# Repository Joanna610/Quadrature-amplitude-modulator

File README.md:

# Quadrature-amplitude-modulator

The goal of the project was to create two devices that would be wirelessly communicating with each other in simplex mode, using quadrature amplitude modulation at the 433 MHz band.

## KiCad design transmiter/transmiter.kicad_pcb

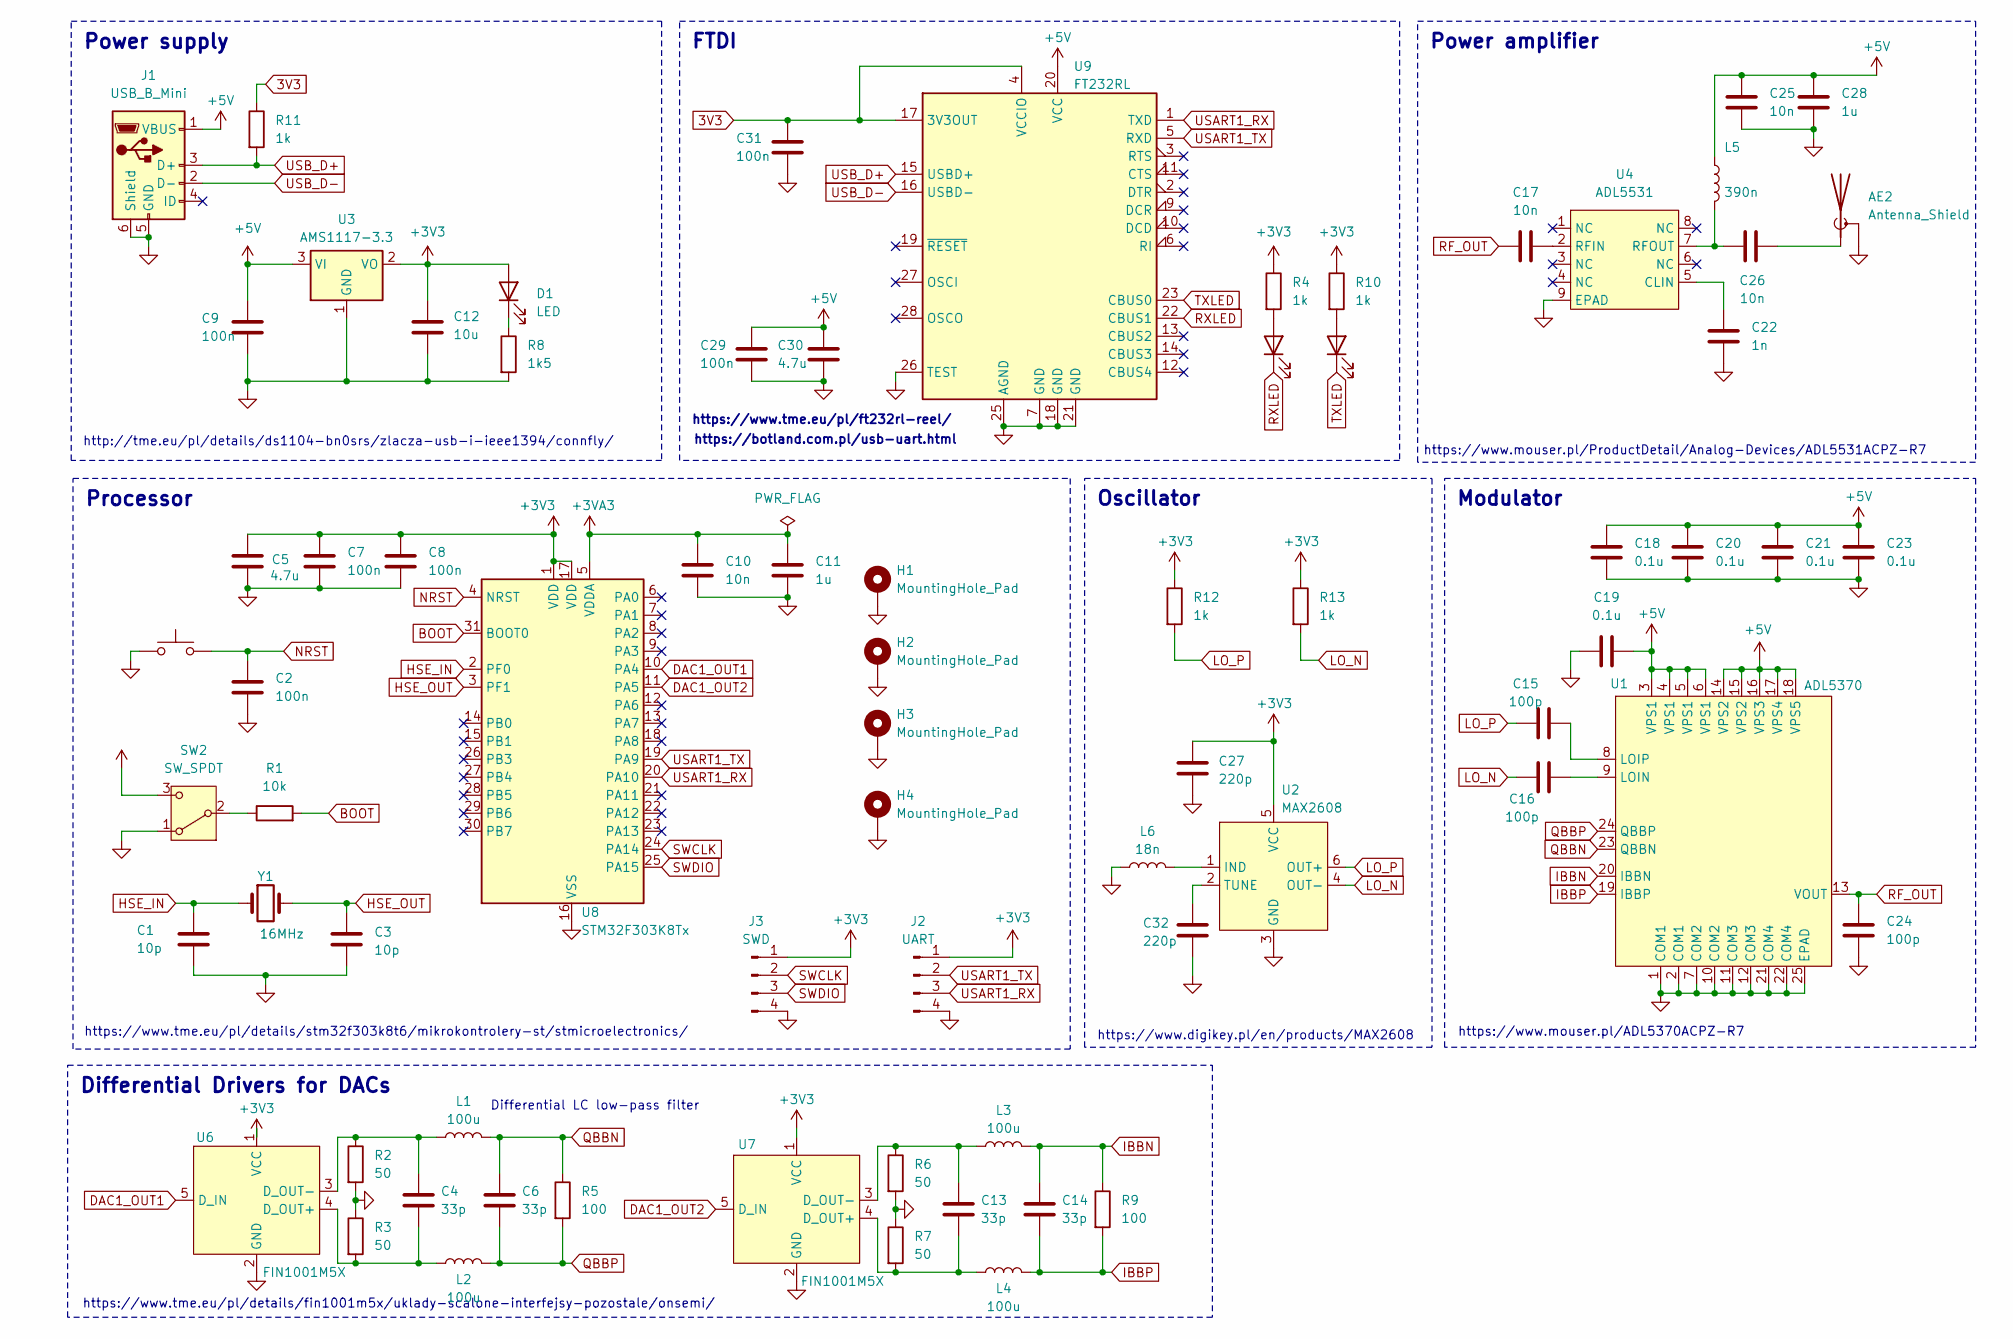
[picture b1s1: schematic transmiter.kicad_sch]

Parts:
AE2: Antenna_Shield; U.FL_Molex_MCRF_73412-0110_Vertical
C1, C3: 10p; C_0603_1608Metric_Pad1.08x0.95mm_HandSolder
C2, C7, C8, C9, C29, C31: 100n; C_0603_1608Metric_Pad1.08x0.95mm_HandSolder
C4, C6, C13, C14: 33p; C_0603_1608Metric_Pad1.08x0.95mm_HandSolder
C5, C30: 4.7u; C_0603_1608Metric_Pad1.08x0.95mm_HandSolder
C10, C25: 10n; C_0603_1608Metric_Pad1.08x0.95mm_HandSolder
C11, C28: 1u; C_0603_1608Metric_Pad1.08x0.95mm_HandSolder
C12: 10u; C_0603_1608Metric_Pad1.08x0.95mm_HandSolder
C15, C16, C24: 100p; C_0402_1005Metric_Pad0.74x0.62mm_HandSolder
C17, C26: 10n; C_0402_1005Metric_Pad0.74x0.62mm_HandSolder
C18, C19, C20, C21, C23: 0.1u; C_0402_1005Metric_Pad0.74x0.62mm_HandSolder
C22: 1n; C_0603_1608Metric_Pad1.08x0.95mm_HandSolder
C27, C32: 220p; C_0603_1608Metric_Pad1.08x0.95mm_HandSolder
D1, D2, D3: LED; LED_0805_2012Metric_Pad1.15x1.40mm_HandSolder
H1, H2, H3, H4: MountingHole_Pad; MountingHole_2.2mm_M2_DIN965_Pad
J1: USB_B_Mini; USB_Mini-B_Lumberg_2486_01_Horizontal
J2: UART; PinHeader_1x04_P2.54mm_Vertical
J3: SWD; PinHeader_1x04_P2.54mm_Vertical
L1, L2, L3, L4: 100u; L_1210_3225Metric_Pad1.42x2.65mm_HandSolder
L5: 390n; L_1008_2520Metric_Pad1.43x2.20mm_HandSolder
L6: 18n; L_0603_1608Metric_Pad1.05x0.95mm_HandSolder
R1: 10k; R_0603_1608Metric_Pad0.98x0.95mm_HandSolder
R2, R3, R6, R7: 50; R_0603_1608Metric_Pad0.98x0.95mm_HandSolder
R4, R10, R11, R12, R13: 1k; R_0603_1608Metric_Pad0.98x0.95mm_HandSolder
R5, R9: 100; R_0603_1608Metric_Pad0.98x0.95mm_HandSolder
R8: 1k5; R_0603_1608Metric_Pad0.98x0.95mm_HandSolder
SW1: SW_Push; PUSH
SW2: SW_SPDT; Nidec_Copal_CAS-120A
U1: ADL5370; LFCSP-24-1EP_4x4mm_P0.5mm_EP2.3x2.3mm
U2: MAX2608; SOT-23-6
U3: AMS1117-3.3; SOT-223-3_TabPin2
U4: ADL5531; LFCSP-8-1EP_3x3mm_P0.5mm_EP1.45x1.74mm
U6, U7: FIN1001M5X; SOT-23-5_HandSoldering
U8: STM32F303K8Tx; LQFP-32_7x7mm_P0.8mm
U9: FT232RL; SSOP-28_5.3x10.2mm_P0.65mm
Y1: 16MHz; Crystal_HC49-4H_Vertical

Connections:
3V3: C31.2, R11.1, U9.4 (VCCIO), U9.17 (3V3OUT)
+3V3: C5.1, C7.1, C8.1, C12.1, C27.2, D1.2 (A), J2.1, J3.1, R4.1, R10.1, R12.1, R13.1, SW2.3 (C), U2.5 (VCC), U3.2 (VO), U6.1 (VCC), U7.1 (VCC), U8.1 (VDD), U8.17 (VDD)
+3VA3: C10.1, C11.1, U8.5 (VDDA)
+5V: C9.2, C18.2, C19.1, C20.2, C21.2, C23.2, C25.1, C28.1, C29.2, C30.2, J1.1 (VBUS), L5.1, U1.3 (VPS1), U1.4 (VPS1), U1.5 (VPS1), U1.6 (VPS1), U1.14 (VPS2), U1.15 (VPS2), U1.16 (VPS3), U1.17 (VPS4), U1.18 (VPS5), U3.3 (VI), U9.20 (VCC)
BOOT: R1.2, U8.31 (BOOT0)
DAC1_OUT1: U6.5 (D_IN), U8.10 (PA4)
DAC1_OUT2: U7.5 (D_IN), U8.11 (PA5)
GND: AE2.2 (Shield), C1.2, C2.2, C3.2, C5.2, C7.2, C8.2, C9.1, C10.2, C11.2, C12.2, C18.1, C19.2, C20.1, C21.1, C22.2, C23.1, C24.2, C25.2, C27.1, C28.2, C29.1, C30.1, C31.1, C32.1, H1.1, H2.1, H3.1, H4.1, J1.5 (GND), J1.6 (Shield), J2.4, J3.4, L6.1, R2.2, R3.1, R6.2, R7.1, R8.2, SW1.1, SW2.1 (A), U1.1 (COM1), U1.2 (COM1), U1.7 (COM2), U1.10 (COM2), U1.11 (COM3), U1.12 (COM3), U1.21 (COM4), U1.22 (COM4), U1.25 (EPAD), U2.3 (GND), U3.1 (GND), U4.9 (EPAD), U6.2 (GND), U7.2 (GND), U8.16 (VSS), U8.32 (VSS), U9.7 (GND), U9.18 (GND), U9.21 (GND), U9.25 (AGND), U9.26 (TEST)
HSE_IN: C1.1, U8.2 (PF0), Y1.1
HSE_OUT: C3.1, U8.3 (PF1), Y1.2
IBBN: C14.1, L3.2, R9.1, U1.20 (IBBN)
IBBP: C14.2, L4.2, R9.2, U1.19 (IBBP)
LO_N: C16.1, R13.2, U2.4 (OUT-)
LO_P: C15.1, R12.2, U2.6 (OUT+)
NRST: C2.1, SW1.2, U8.4 (NRST)
unnamed: AE2.1 (A), C26.2
unnamed: D1.1 (K), R8.1
unnamed: D2.2 (A), R4.2
unnamed: D3.2 (A), R10.2
unnamed: R1.1, SW2.2 (B)
unnamed: C16.2, U1.9 (LOIN)
unnamed: C15.2, U1.8 (LOIP)
unnamed: L6.2, U2.1 (IND)
unnamed: C32.2, U2.2 (TUNE)
unnamed: C22.1, U4.5 (CLIN)
unnamed: C17.2, U4.2 (RFIN)
unnamed: C26.1, L5.2, U4.7 (RFOUT)
unnamed: C4.2, L2.1, R3.2, U6.4 (D_OUT+)
unnamed: C4.1, L1.1, R2.1, U6.3 (D_OUT-)
unnamed: C13.2, L4.1, R7.2, U7.4 (D_OUT+)
unnamed: C13.1, L3.1, R6.1, U7.3 (D_OUT-)
QBBN: C6.1, L1.2, R5.1, U1.23 (QBBN)
QBBP: C6.2, L2.2, R5.2, U1.24 (QBBP)
RF_OUT: C17.1, C24.1, U1.13 (VOUT)
RXLED: D2.1 (K), U9.22 (CBUS1)
SWCLK: J3.2, U8.24 (PA14)
SWDIO: J3.3, U8.25 (PA15)
TXLED: D3.1 (K), U9.23 (CBUS0)
USART1_RX: J2.3, U8.20 (PA10), U9.1 (TXD)
USART1_TX: J2.2, U8.19 (PA9), U9.5 (RXD)
USB_D+: J1.3 (D+), R11.2, U9.15 (USBD+)
USB_D-: J1.2 (D-), U9.16 (USBD-)

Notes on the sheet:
Oscillator
Power amplifier
Processor
Differential Drivers for DACs
FTDI
Power supply
Modulator
https://www.digikey.pl/en/products/MAX2608
Differential LC low-pass filter
https://www.tme.eu/pl/ft232rl-reel/
https://www.mouser.pl/ProductDetail/Analog-Devices/ADL5531ACPZ-R7
https://www.tme.eu/pl/details/fin1001m5x/uklady-scalone-interfejsy-pozostale/onsemi/
https://www.mouser.pl/ADL5370ACPZ-R7
https://botland.com.pl/usb-uart.html
https://www.tme.eu/pl/details/stm32f303k8t6/mikrokontrolery-st/stmicroelectronics/
http://tme.eu/pl/details/ds1104-bn0srs/zlacza-usb-i-ieee1394/connfly/

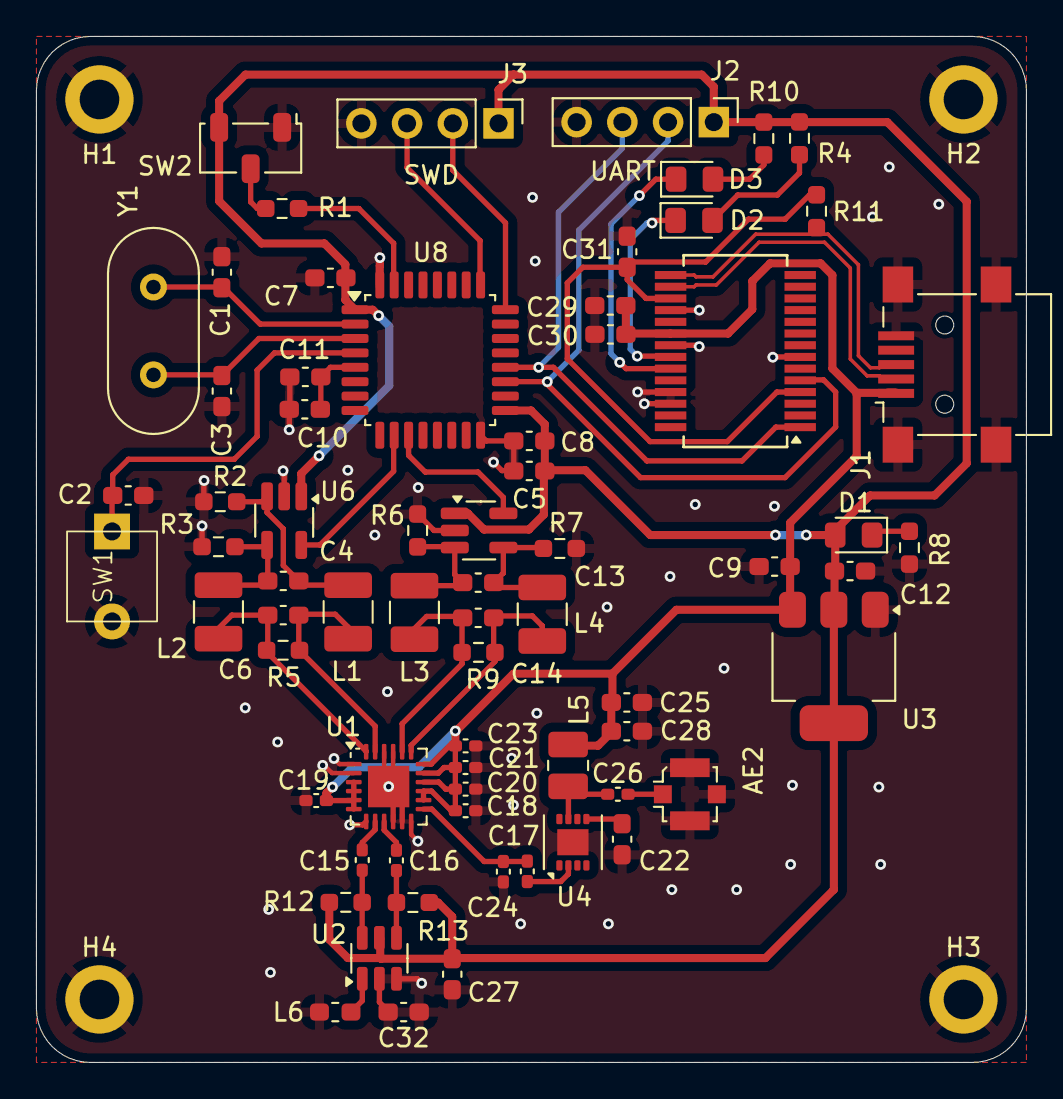
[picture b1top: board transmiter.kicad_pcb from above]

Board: 2 copper layers, 55.0 x 57.0 mm, 73 parts (0 on the bottom side), 42 nets.

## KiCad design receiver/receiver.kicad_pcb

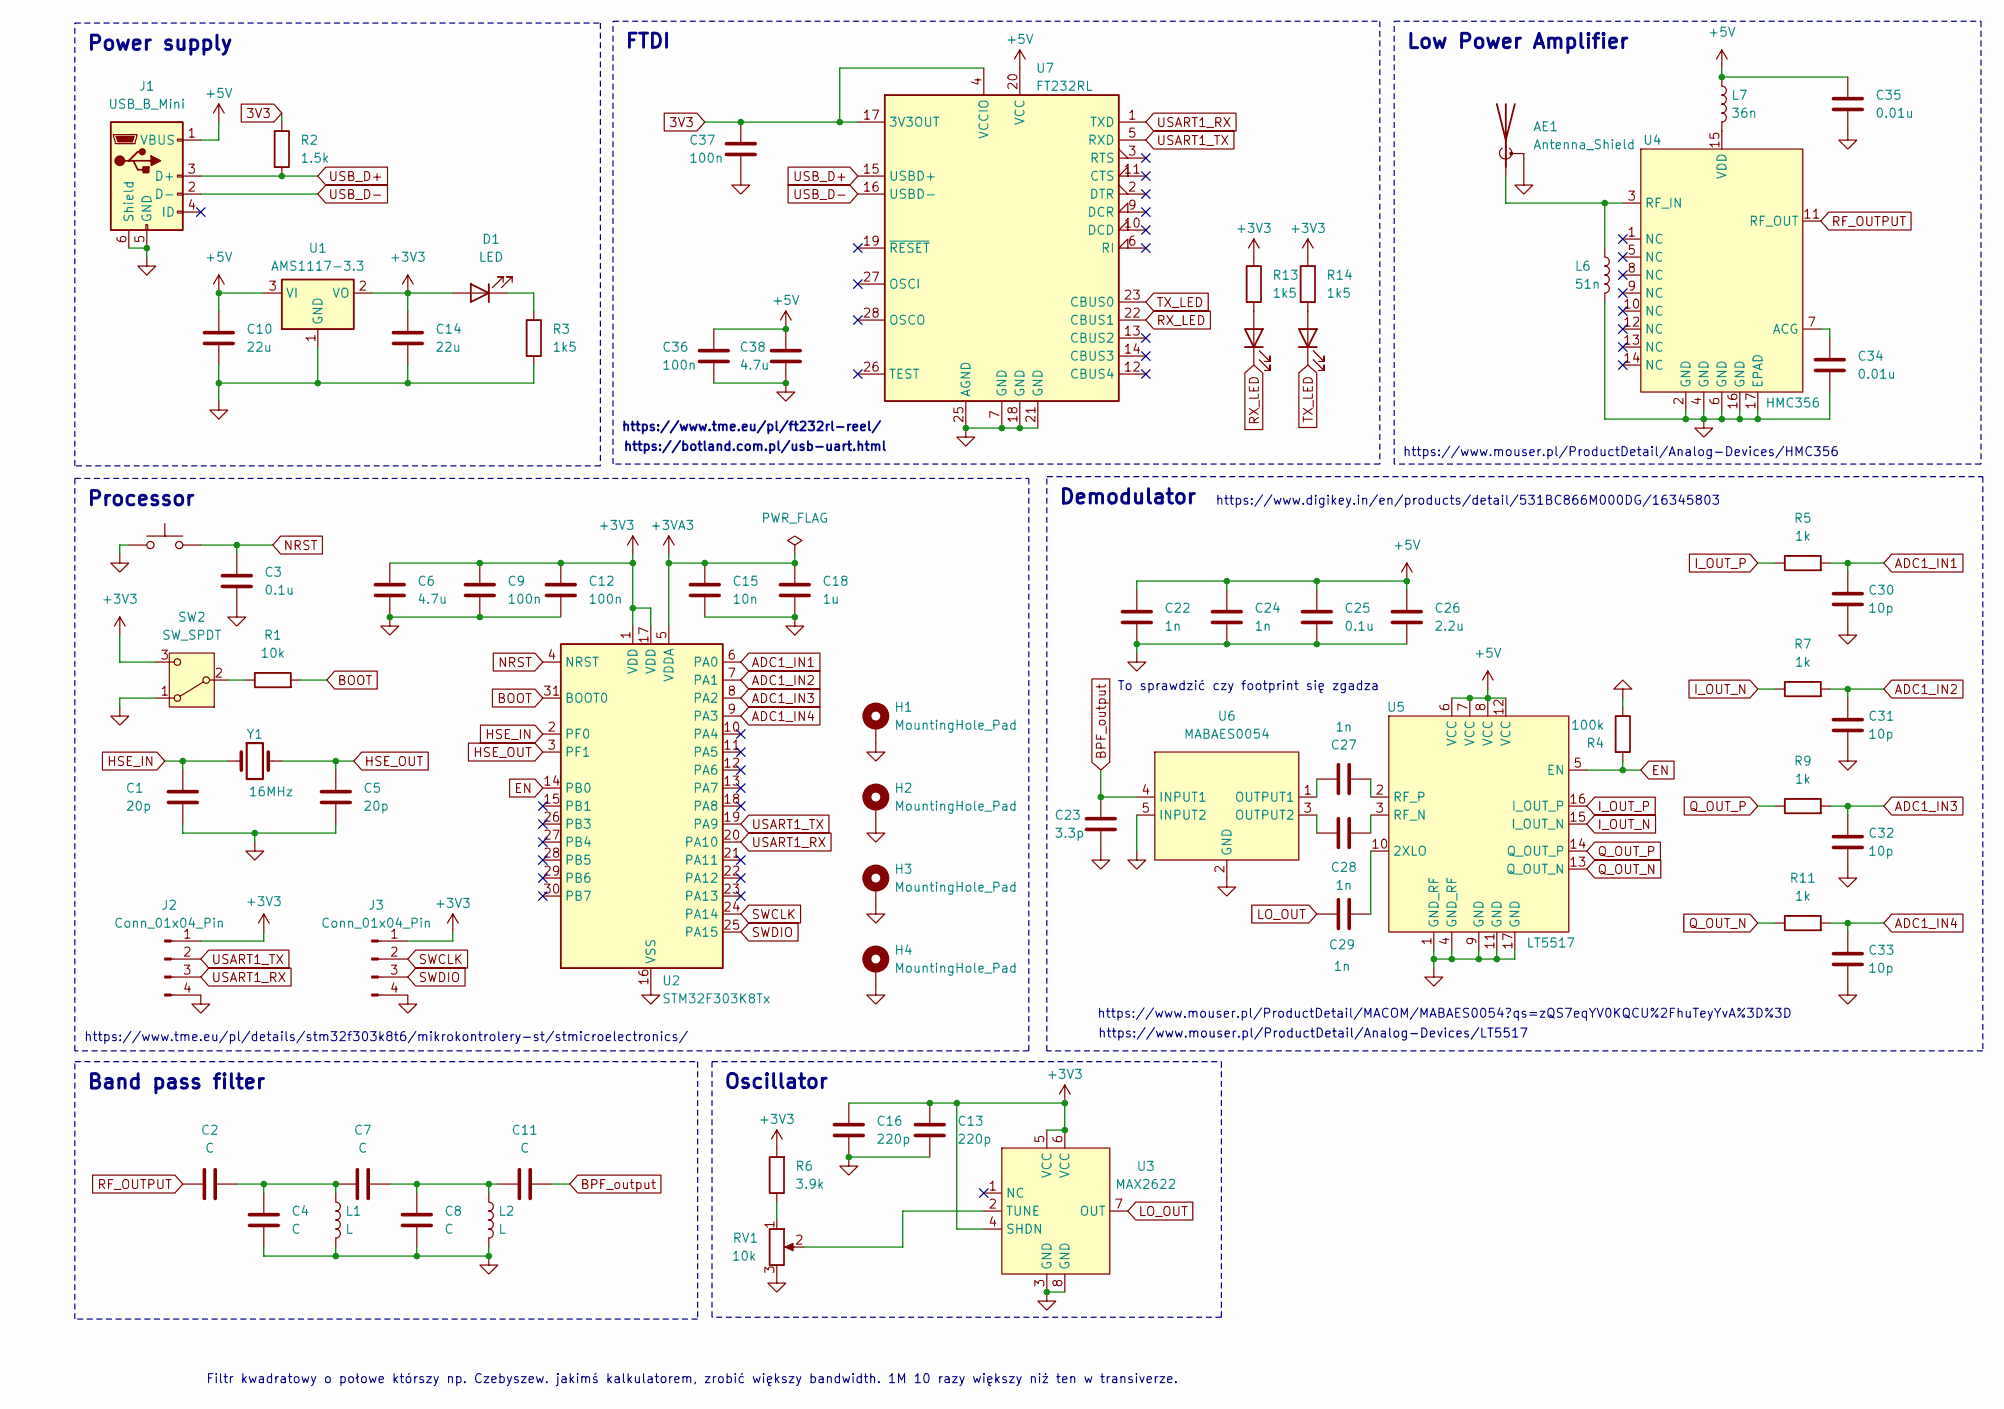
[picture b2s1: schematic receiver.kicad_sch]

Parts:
AE1: Antenna_Shield; U.FL_Molex_MCRF_73412-0110_Vertical
C1, C5: 20p; C_0603_1608Metric_Pad1.08x0.95mm_HandSolder
C2, C4, C7, C8, C11: C; C_0603_1608Metric_Pad1.08x0.95mm_HandSolder
C3, C25: 0.1u; C_0603_1608Metric_Pad1.08x0.95mm_HandSolder
C6, C38: 4.7u; C_0603_1608Metric_Pad1.08x0.95mm_HandSolder
C9, C12, C36, C37: 100n; C_0603_1608Metric_Pad1.08x0.95mm_HandSolder
C10, C14: 22u; C_0603_1608Metric_Pad1.08x0.95mm_HandSolder
C13, C16: 220p; C_0603_1608Metric_Pad1.08x0.95mm_HandSolder
C15: 10n; C_0603_1608Metric_Pad1.08x0.95mm_HandSolder
C18: 1u; C_0603_1608Metric_Pad1.08x0.95mm_HandSolder
C22, C24, C27, C28, C29: 1n; C_0603_1608Metric_Pad1.08x0.95mm_HandSolder
C23: 3.3p; C_0603_1608Metric_Pad1.08x0.95mm_HandSolder
C26: 2.2u; C_0603_1608Metric_Pad1.08x0.95mm_HandSolder
C30, C31, C32, C33: 10p; C_0805_2012Metric_Pad1.18x1.45mm_HandSolder
C34, C35: 0.01u; C_0603_1608Metric_Pad1.08x0.95mm_HandSolder
D1, D2, D3: LED; LED_0805_2012Metric_Pad1.15x1.40mm_HandSolder
H1, H2, H3, H4: MountingHole_Pad; MountingHole_2.2mm_M2_DIN965_Pad
J1: USB_B_Mini; USB_Mini-B_Lumberg_2486_01_Horizontal
J2, J3: Conn_01x04_Pin; PinHeader_1x04_P2.54mm_Vertical
L1, L2: L; L_0603_1608Metric_Pad1.05x0.95mm_HandSolder
L6: 51n; L_0603_1608Metric_Pad1.05x0.95mm_HandSolder
L7: 36n; L_0603_1608Metric_Pad1.05x0.95mm_HandSolder
R1: 10k; R_0603_1608Metric_Pad0.98x0.95mm_HandSolder
R2: 1.5k; R_0603_1608Metric_Pad0.98x0.95mm_HandSolder
R3, R13, R14: 1k5; R_0603_1608Metric_Pad0.98x0.95mm_HandSolder
R4: 100k; R_0603_1608Metric_Pad0.98x0.95mm_HandSolder
R5, R7, R9, R11: 1k; R_0603_1608Metric_Pad0.98x0.95mm_HandSolder
R6: 3.9k; R_0603_1608Metric_Pad0.98x0.95mm_HandSolder
RV1: 10k; Potentiometer_Bourns_TC33X_Vertical
SW1: SW_Push; PUSH
SW2: SW_SPDT; Nidec_Copal_CAS-120A
U1: AMS1117-3.3; SOT-223-3_TabPin2
U2: STM32F303K8Tx; LQFP-32_7x7mm_P0.8mm
U3: MAX2622; TSSOP-8_4.4x3mm_P0.65mm
U4: HMC356; QFN-16-1EP_3x3mm_P0.5mm_EP1.45x1.45mm
U5: LT5517; QFN-16-1EP_4x4mm_P0.65mm_EP2.1x2.1mm
U6: MABAES0054; Transformer_MACOM_SM-22
U7: FT232RL; SSOP-28_5.3x10.2mm_P0.65mm
Y1: 16MHz; Crystal_HC49-4H_Vertical

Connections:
3V3: C37.2, R2.1, U7.4 (VCCIO), U7.17 (3V3OUT)
+3V3: C6.1, C9.1, C12.1, C13.1, C14.1, C16.1, D1.2 (A), J2.1, J3.1, R6.2, R13.1, R14.1, SW2.3 (C), U1.2 (VO), U2.1 (VDD), U2.17 (VDD), U3.4 (SHDN), U3.5 (VCC), U3.6 (VCC)
+3VA3: C15.1, C18.1, U2.5 (VDDA)
+5V: C10.1, C22.1, C24.1, C25.1, C26.1, C35.1, C36.2, C38.2, J1.1 (VBUS), L7.1, U1.3 (VI), U5.6 (VCC), U5.7 (VCC), U5.8 (VCC), U5.12 (VCC), U7.20 (VCC)
ADC1_IN1: C30.1, R5.2, U2.6 (PA0)
ADC1_IN2: C31.1, R7.2, U2.7 (PA1)
ADC1_IN3: C32.1, R9.2, U2.8 (PA2)
ADC1_IN4: C33.1, R11.2, U2.9 (PA3)
BOOT: R1.2, U2.31 (BOOT0)
BPF_output: C11.2, C23.1, U6.4 (INPUT1)
EN: R4.2, U2.14 (PB0), U5.5 (EN)
GND: AE1.2 (Shield), C1.2, C3.2, C4.1, C5.2, C6.2, C8.1, C9.2, C10.2, C12.2, C13.2, C14.2, C15.2, C16.2, C18.2, C22.2, C23.2, C24.2, C25.2, C26.2, C30.2, C31.2, C32.2, C33.2, C34.2, C35.2, C36.1, C37.1, C38.1, H1.1, H2.1, H3.1, H4.1, J1.5 (GND), J1.6 (Shield), J2.4, J3.4, L1.2, L2.2, L6.2, R3.2, R4.1, RV1.3, SW1.1, SW2.1 (A), U1.1 (GND), U2.16 (VSS), U2.32 (VSS), U3.3 (GND), U3.8 (GND), U4.2 (GND), U4.4 (GND), U4.6 (GND), U4.16 (GND), U4.17 (EPAD), U5.1 (GND_RF), U5.4 (GND_RF), U5.9 (GND), U5.11 (GND), U5.17 (GND), U6.2 (GND), U6.5 (INPUT2), U7.7 (GND), U7.18 (GND), U7.21 (GND), U7.25 (AGND)
HSE_IN: C1.1, U2.2 (PF0), Y1.1
HSE_OUT: C5.1, U2.3 (PF1), Y1.2
I_OUT_N: R7.1, U5.15 (I_OUT_N)
I_OUT_P: R5.1, U5.16 (I_OUT_P)
LO_OUT: C29.2, U3.7 (OUT)
NRST: C3.1, SW1.2, U2.4 (NRST)
unnamed: AE1.1 (A), L6.1, U4.3 (RF_IN)
unnamed: C2.2, C4.2, C7.1, L1.1
unnamed: C7.2, C8.2, C11.1, L2.1
unnamed: D1.1 (K), R3.1
unnamed: D2.2 (A), R13.2
unnamed: D3.2 (A), R14.2
unnamed: R6.1, RV1.1
unnamed: R1.1, SW2.2 (B)
unnamed: RV1.2, U3.2 (TUNE)
unnamed: C34.1, U4.7 (ACG)
unnamed: L7.2, U4.15 (VDD)
unnamed: C29.1, U5.10 (2XLO)
unnamed: C28.1, U5.3 (RF_N)
unnamed: C27.2, U5.2 (RF_P)
unnamed: C27.1, U6.1 (OUTPUT1)
unnamed: C28.2, U6.3 (OUTPUT2)
Q_OUT_N: R11.1, U5.13 (Q_OUT_N)
Q_OUT_P: R9.1, U5.14 (Q_OUT_P)
RF_OUTPUT: C2.1, U4.11 (RF_OUT)
RX_LED: D2.1 (K), U7.22 (CBUS1)
SWCLK: J3.2, U2.24 (PA14)
SWDIO: J3.3, U2.25 (PA15)
TX_LED: D3.1 (K), U7.23 (CBUS0)
USART1_RX: J2.3, U2.20 (PA10), U7.1 (TXD)
USART1_TX: J2.2, U2.19 (PA9), U7.5 (RXD)
USB_D+: J1.3 (D+), R2.2, U7.15 (USBD+)
USB_D-: J1.2 (D-), U7.16 (USBD-)

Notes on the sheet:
Oscillator
Low Power Amplifier
Power supply
FTDI
Demodulator
Band pass filter
Processor
https://www.digikey.in/en/products/detail/531BC866M000DG/16345803
https://www.mouser.pl/ProductDetail/Analog-Devices/HMC356
To sprawdzić czy footprint się zgadza
https://www.mouser.pl/ProductDetail/Analog-Devices/LT5517
https://botland.com.pl/usb-uart.html
https://www.tme.eu/pl/ft232rl-reel/
https://www.tme.eu/pl/details/stm32f303k8t6/mikrokontrolery-st/stmicroelectronics/
Filtr kwadratowy o połowe którszy np. Czebyszew. jakimś kalkulatorem, zrobić większy bandwidth. 1M 10 razy większy niż ten w transiverze.
https://www.mouser.pl/ProductDetail/MACOM/MABAES0054?qs=zQS7eqYV0KQCU%2FhuTeyYvA%3D%3D

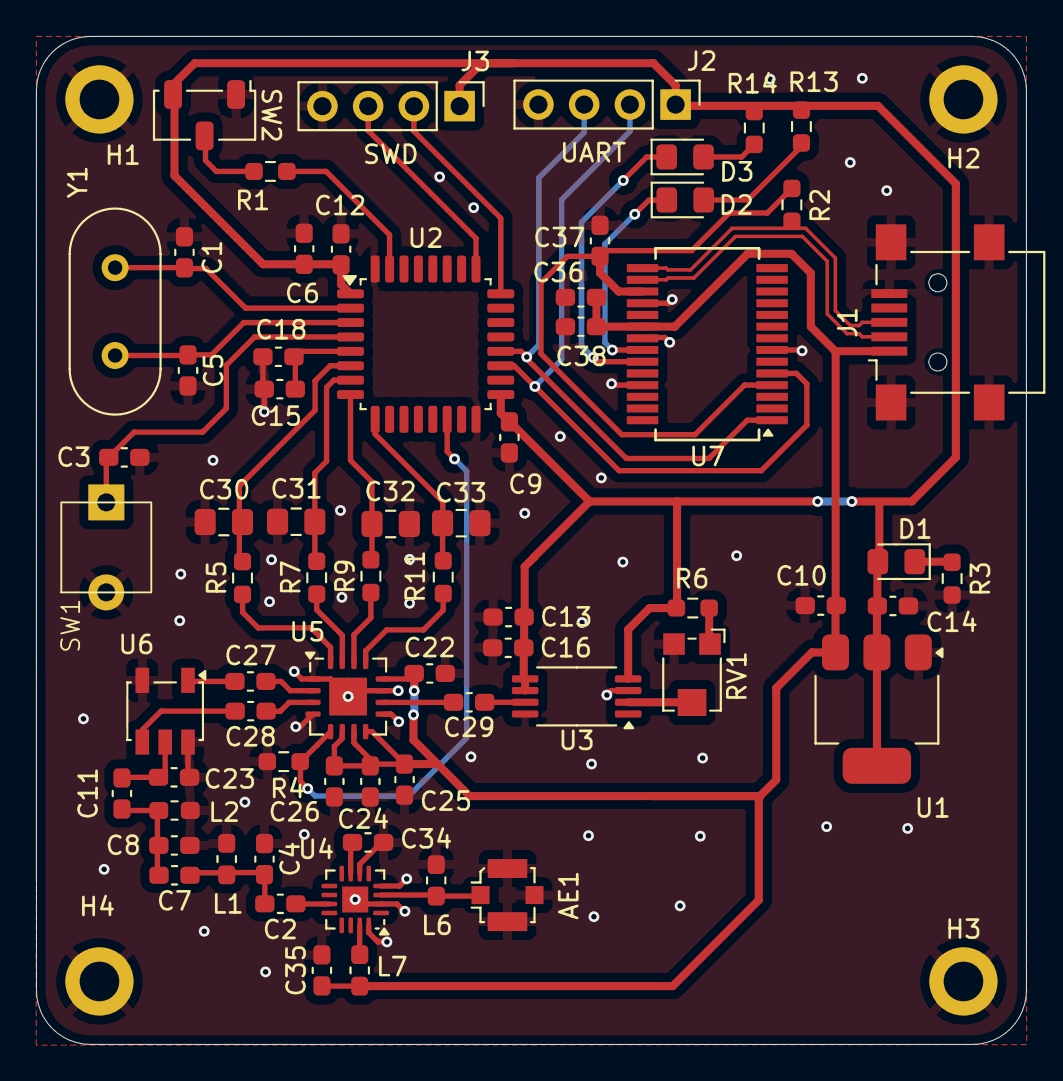
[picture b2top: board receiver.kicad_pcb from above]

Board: 2 copper layers, 55.0 x 56.0 mm, 71 parts (0 on the bottom side), 45 nets.

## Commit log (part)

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2026-02-28 KiCad schematic design
2026-03-20 First stage of PCB design
2026-03-29 Finished PCB design
2026-04-06 First design of sended PCBs
2026-04-19 Correction to PCBs
